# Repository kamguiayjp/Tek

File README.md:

# Tek
files for the ten smartwatch design

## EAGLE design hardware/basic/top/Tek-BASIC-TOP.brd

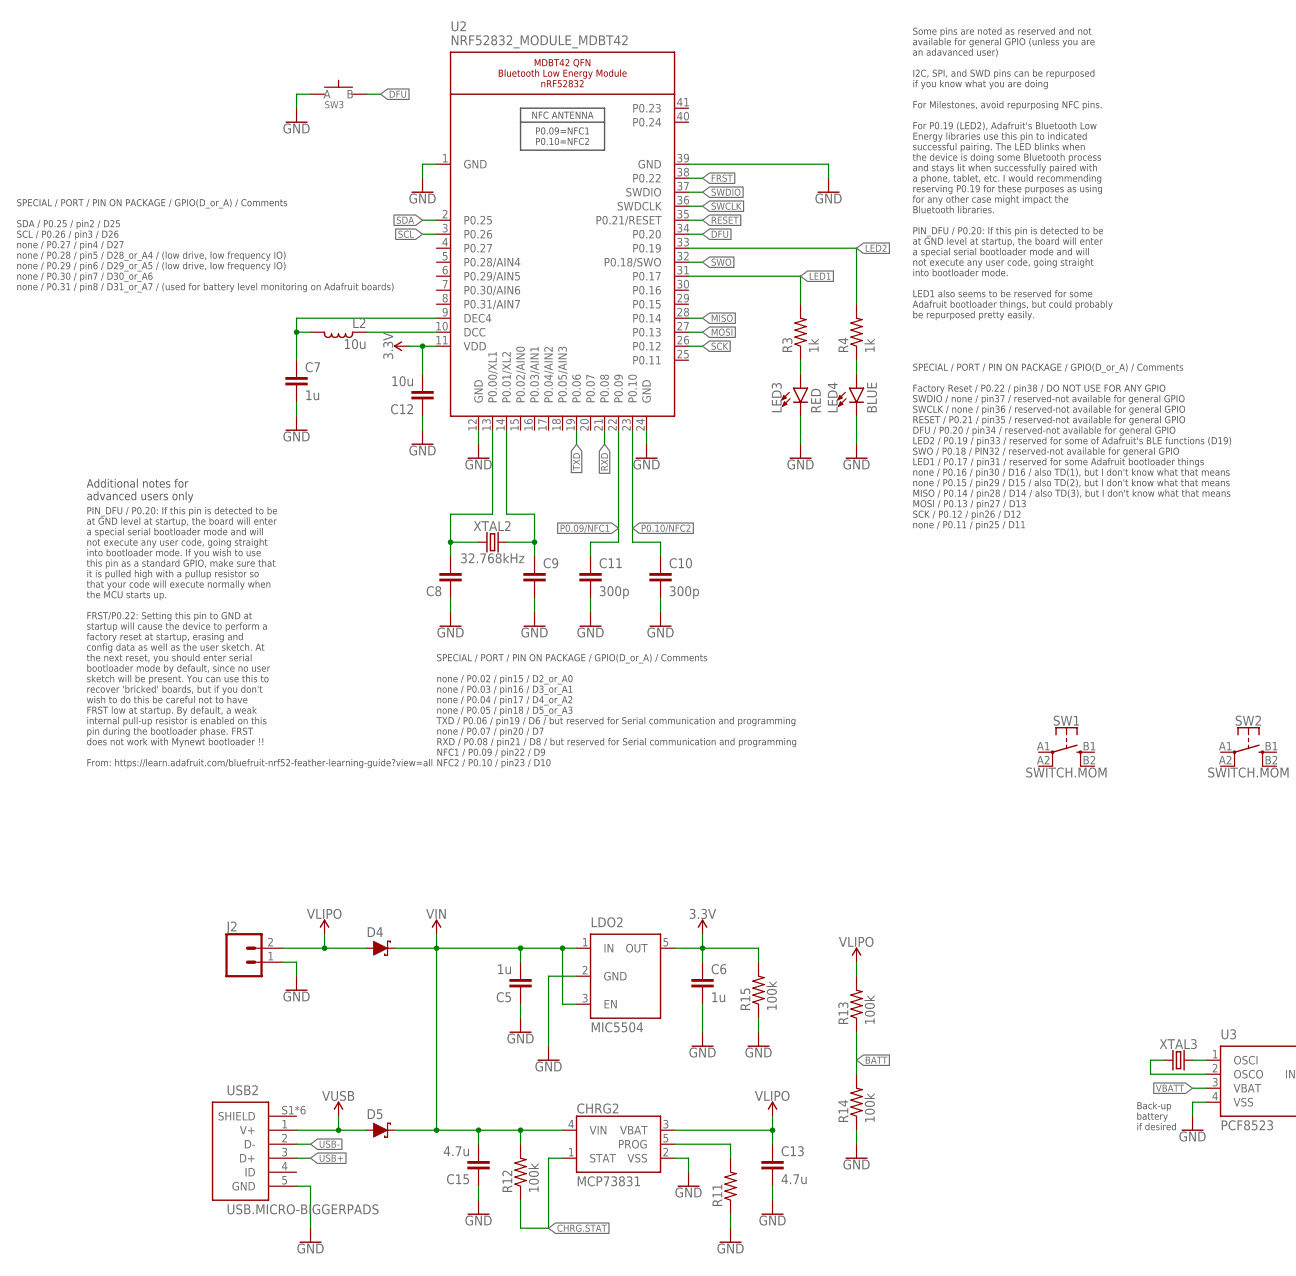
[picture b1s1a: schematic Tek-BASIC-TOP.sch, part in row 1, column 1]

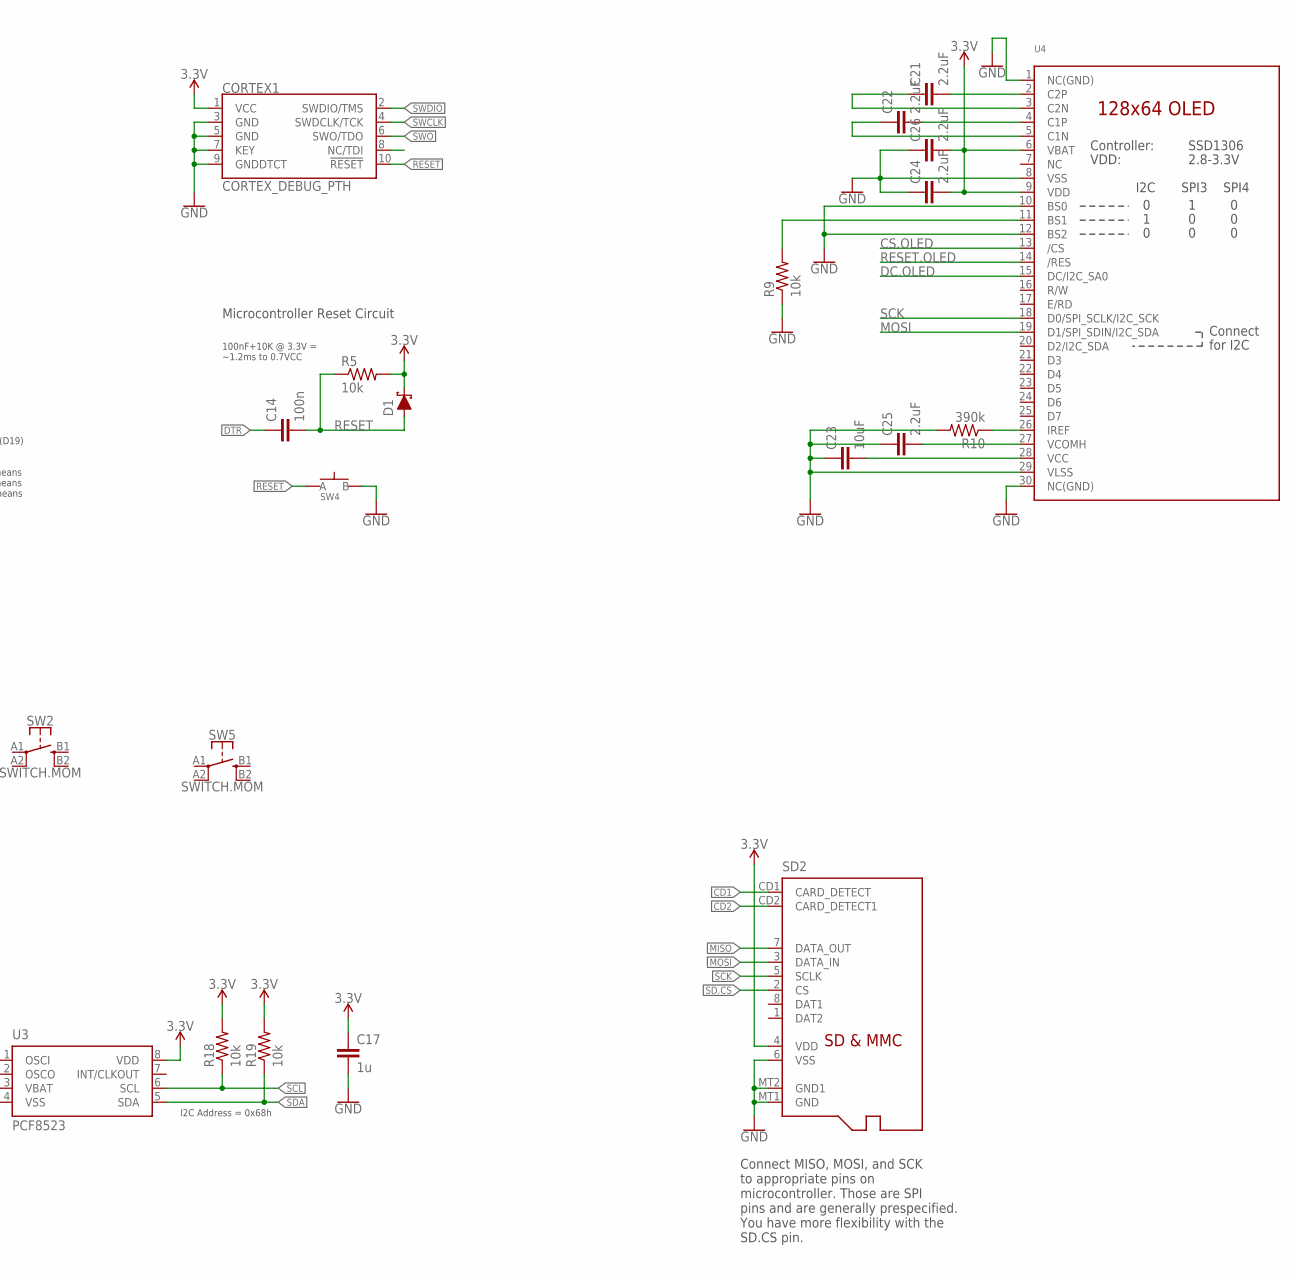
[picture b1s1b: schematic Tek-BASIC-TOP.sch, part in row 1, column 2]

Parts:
C5, C6, C7, C17: 1u; C0603
C8, C9: CAPACITOR0603; C0603
C10, C11: 300p; C0603
C12: 10u; C0805
C13, C15: 4.7u; C0603
C14: 100n; C0603
C21, C22, C24, C25, C26: 2.2uF; C0402
C23: 10uF; C0603
CHRG2: MCP73831; SOT23-5
CORTEX1: CORTEX_DEBUG_PTH; 2X5-PTH-1.27MM
D1, D4, D5: SCHOTTKY-USC; USC
J2: CONN_02; 1X02
L2: 10u; L0603
LDO2: MIC5504; SOT23-5
LED3: RED; LED-0603
LED4: BLUE; LED-0603
R3, R4: 1k; R0603
R5, R9, R18, R19: 10k; R0603
R10: 390k; R0603
R11: RESISTOR0603; R0603
R12, R13, R14, R15: 100k; R0603
SD2: MICROSD
SW1, SW2, SW5: SWITCH.MOM; TACTILE_SWITCH_SMD_6.2MM_TALL
SW3, SW4: SPST-PTS830GG140-COPY.1-3; BUTTON-GULLWING
U2: NRF52832_MODULE_MDBT42; BLE_MODULE_RAYTAC_MDBT42
U3: PCF8523; SO8; DIGIKEY 568-5306-1-ND
U4: DISP_OLED_UG-2864HSWEG01-NO-WRAPAROUND; UG-2864HSWEG01_0.96IN_NO-WRAPAROUND
USB2: USB.MICRO-BIGGERPADS; USB-MICRO-01.BIGGERPADS
XTAL2: 32.768kHz; 2-SMD.NOLEAD.2.0MMTO1.2MM
XTAL3: 32.7680kHz; 2-SMD.NOLEAD.2.0MMTO1.2MM

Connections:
3.3V: C6.1, C12.2, C17.1, C24.2, C26.2, CORTEX1.1 (VCC), D1.- (C), LDO2.5 (OUT), R5.2, R15.2, R18.2, R19.2, SD2.4 (VDD), U2.11 (VDD), U3.8 (VDD), U4.6 (VBAT), U4.9 (VDD)
BATT: R13.1, R14.2
CD1: SD2.CD1 (CARD_DETECT)
CD2: SD2.CD2 (CARD_DETECT1)
CHRG.STAT: CHRG2.1 (STAT), R12.1
CS.OLED: U4.13 (/CS)
DC.OLED: U4.15 (DC/I2C_SA0)
DFU: SW3.3 (B), U2.34 (P0.20)
DTR: C14.1
FRST: U2.38 (P0.22)
GND: C5.1, C6.2, C7.2, C8.1, C9.2, C10.2, C11.2, C12.1, C13.2, C15.1, C17.2, C23.1, C24.1, C25.1, C26.1, CHRG2.2 (VSS), CORTEX1.3 (GND), CORTEX1.5 (GND), CORTEX1.7 (KEY), CORTEX1.9 (GNDDTCT), J2.1, LDO2.2 (GND), LED3.C, LED4.C, R9.1, R10.2, R11.1, R14.1, R15.1, SD2.6 (VSS), SD2.MT1 (GND), SD2.MT2 (GND1), SW3.1 (A), SW4.3 (B), U2.1 (GND), U2.12 (GND), U2.24 (GND), U2.39 (GND), U3.4 (VSS), U4.1 (NC(GND)), U4.8 (VSS), U4.10 (BS0), U4.12 (BS2), U4.29 (VLSS), U4.30 (NC(GND)), USB2.5 (GND)
LED1: R3.2, U2.31 (P0.17)
LED2: R4.2, U2.33 (P0.19)
MISO: SD2.7 (DATA_OUT), U2.28 (P0.14)
MOSI: SD2.3 (DATA_IN), U2.27 (P0.13), U4.19 (D1/SPI_SDIN/I2C_SDA)
unnamed: CHRG2.5 (PROG), R11.2
unnamed: C8.2, U2.13 (P0.00/XL1), XTAL2.P$1 (1)
unnamed: U3.2 (OSCO), XTAL3.P$1 (1)
unnamed: C9.1, U2.14 (P0.01/XL2), XTAL2.P$2 (2)
unnamed: U3.1 (OSCI), XTAL3.P$2 (2)
unnamed: LED3.A, R3.1
unnamed: LED4.A, R4.1
unnamed: L2.1, U2.10 (DCC)
unnamed: C7.1, L2.2, U2.9 (DEC4)
unnamed: R9.2, U4.11 (BS1)
unnamed: R10.1, U4.26 (IREF)
unnamed: C21.2, U4.2 (C2P)
unnamed: C21.1, U4.3 (C2N)
unnamed: C22.2, U4.4 (C1P)
unnamed: C22.1, U4.5 (C1N)
unnamed: C23.2, U4.28 (VCC)
unnamed: C25.2, U4.27 (VCOMH)
P0.09/NFC1: C11.1, U2.22 (P0.09)
P0.10/NFC2: C10.1, U2.23 (P0.10)
RESET: C14.2, CORTEX1.10 (!RESET), D1.+ (A), R5.1, SW4.1 (A), U2.35 (P0.21/RESET)
RESET.OLED: U4.14 (/RES)
RXD: U2.21 (P0.08)
SCK: SD2.5 (SCLK), U2.26 (P0.12), U4.18 (D0/SPI_SCLK/I2C_SCK)
SCL: R18.1, U2.3 (P0.26), U3.6 (SCL)
SD.CS: SD2.2 (CS)
SDA: R19.1, U2.2 (P0.25), U3.5 (SDA)
SWCLK: CORTEX1.4 (SWDCLK/TCK), U2.36 (SWDCLK)
SWDIO: CORTEX1.2 (SWDIO/TMS), U2.37 (SWDIO)
SWO: CORTEX1.6 (SWO/TDO), U2.32 (P0.18/SWO)
TXD: U2.19 (P0.06)
USB+: USB2.3 (D+)
USB-: USB2.2 (D-)
VBATT: U3.3 (VBAT)
VIN: C5.2, C15.2, CHRG2.4 (VIN), D4.- (C), D5.- (C), LDO2.1 (IN), LDO2.3 (EN), R12.2
VLIPO: C13.1, CHRG2.3 (VBAT), D4.+ (A), J2.2, R13.2
V_USB: D5.+ (A), USB2.1 (V+)

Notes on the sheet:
Microcontroller Reset Circuit
100nF+10K @ 3.3V = ~1.2ms to 0.7VCC
SPECIAL / PORT / PIN ON PACKAGE / GPIO(D_or_A) / Comments SDA / P0.25 / pin2 / D25 SCL / P0.26 / pin3 / D26 none / P0.27 / pin4 / D27 none / P0.28 / pin5 / D28_or_A4 / (low drive, low frequency IO) none / P0.29 / pin6 / D29_or_A5 / (low drive, low frequency IO) none / P0.30 / pin7 / D30_or_A6 none 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
SPECIAL / PORT / PIN ON PACKAGE / GPIO(D_or_A) / Comments none / P0.02 / pin15 / D2_or_A0 none / P0.03 / pin16 / D3_or_A1 none / P0.04 / pin17 / D4_or_A2 none / P0.05 / pin18 / D5_or_A3 TXD / P0.06 / pin19 / D6 / but reserved for Serial communication and programming none / P0.07 / pin20 / D7 RXD / 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
SPECIAL / PORT / PIN ON PACKAGE / GPIO(D_or_A) / Comments Factory Reset / P0.22 / pin38 / DO NOT USE FOR ANY GPIO SWDIO / none / pin37 / reserved-not available for general GPIO SWCLK / none / pin36 / reserved-not available for general GPIO RESET / P0.21 / pin35 / reserved-not available for general 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
Some pins are noted as reserved and not available for general GPIO (unless you are an adavanced user) I2C, SPI, and SWD pins can be repurposed if you know what you are doing For Milestones, avoid repurposing NFC pins. For P0.19 (LED2), Adafruit's Bluetooth Low Energy libraries use this pin to indic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
PIN_DFU / P0.20: If this pin is detected to be at GND level at startup, the board will enter a special serial bootloader mode and will not execute any user code, going straight into bootloader mode. If you wish to use this pin as a standard GPIO, make sure that it is pulled high with a pullup resis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
Additional notes for advanced users only
I2C Address = 0x68h
Back-up battery if desired
Connect MISO, MOSI, and SCK to appropriate pins on microcontroller. Those are SPI pins and are generally prespecified. You have more flexibility with the SD.CS pin.

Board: 2 copper layers, 52 parts (2 on the bottom side), 38 nets, no tracks yet.

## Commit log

2020-06-30 added the tek smartwatch features word document
2020-07-14 arduino files
2020-07-14 added hardware files
2020-07-15 Upload ot the udpdates made on the top board design: base items added on the schematic and on the board
